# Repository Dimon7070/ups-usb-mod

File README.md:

### Modification in progress
Plans:
- [x] Added Gerber and BOM for original schematic
- [x] Added schematic, Gerber and BOM for 0402 smd parts and ADUM1201 isolator
- [ ] add scematics with SMD sizes that are more hand-soldering friendly.
- [ ] add gerber files 
- [ ] add wiki with explanation about USB-Serial IC setup

# original README
# ups-usb
This repo contains the isolated USB to serial board that I designed for a Serioux LD600LI UPS to get it to talk reliably with NUT.
Project was designed using Kicad V8.  For more information check out [Voltlog #503](https://youtu.be/ZeoCBQmW2Rw)

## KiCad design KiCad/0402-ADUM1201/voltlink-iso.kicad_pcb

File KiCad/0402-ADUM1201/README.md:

Schematics with 0402 smd components and ADUM1201 isolator

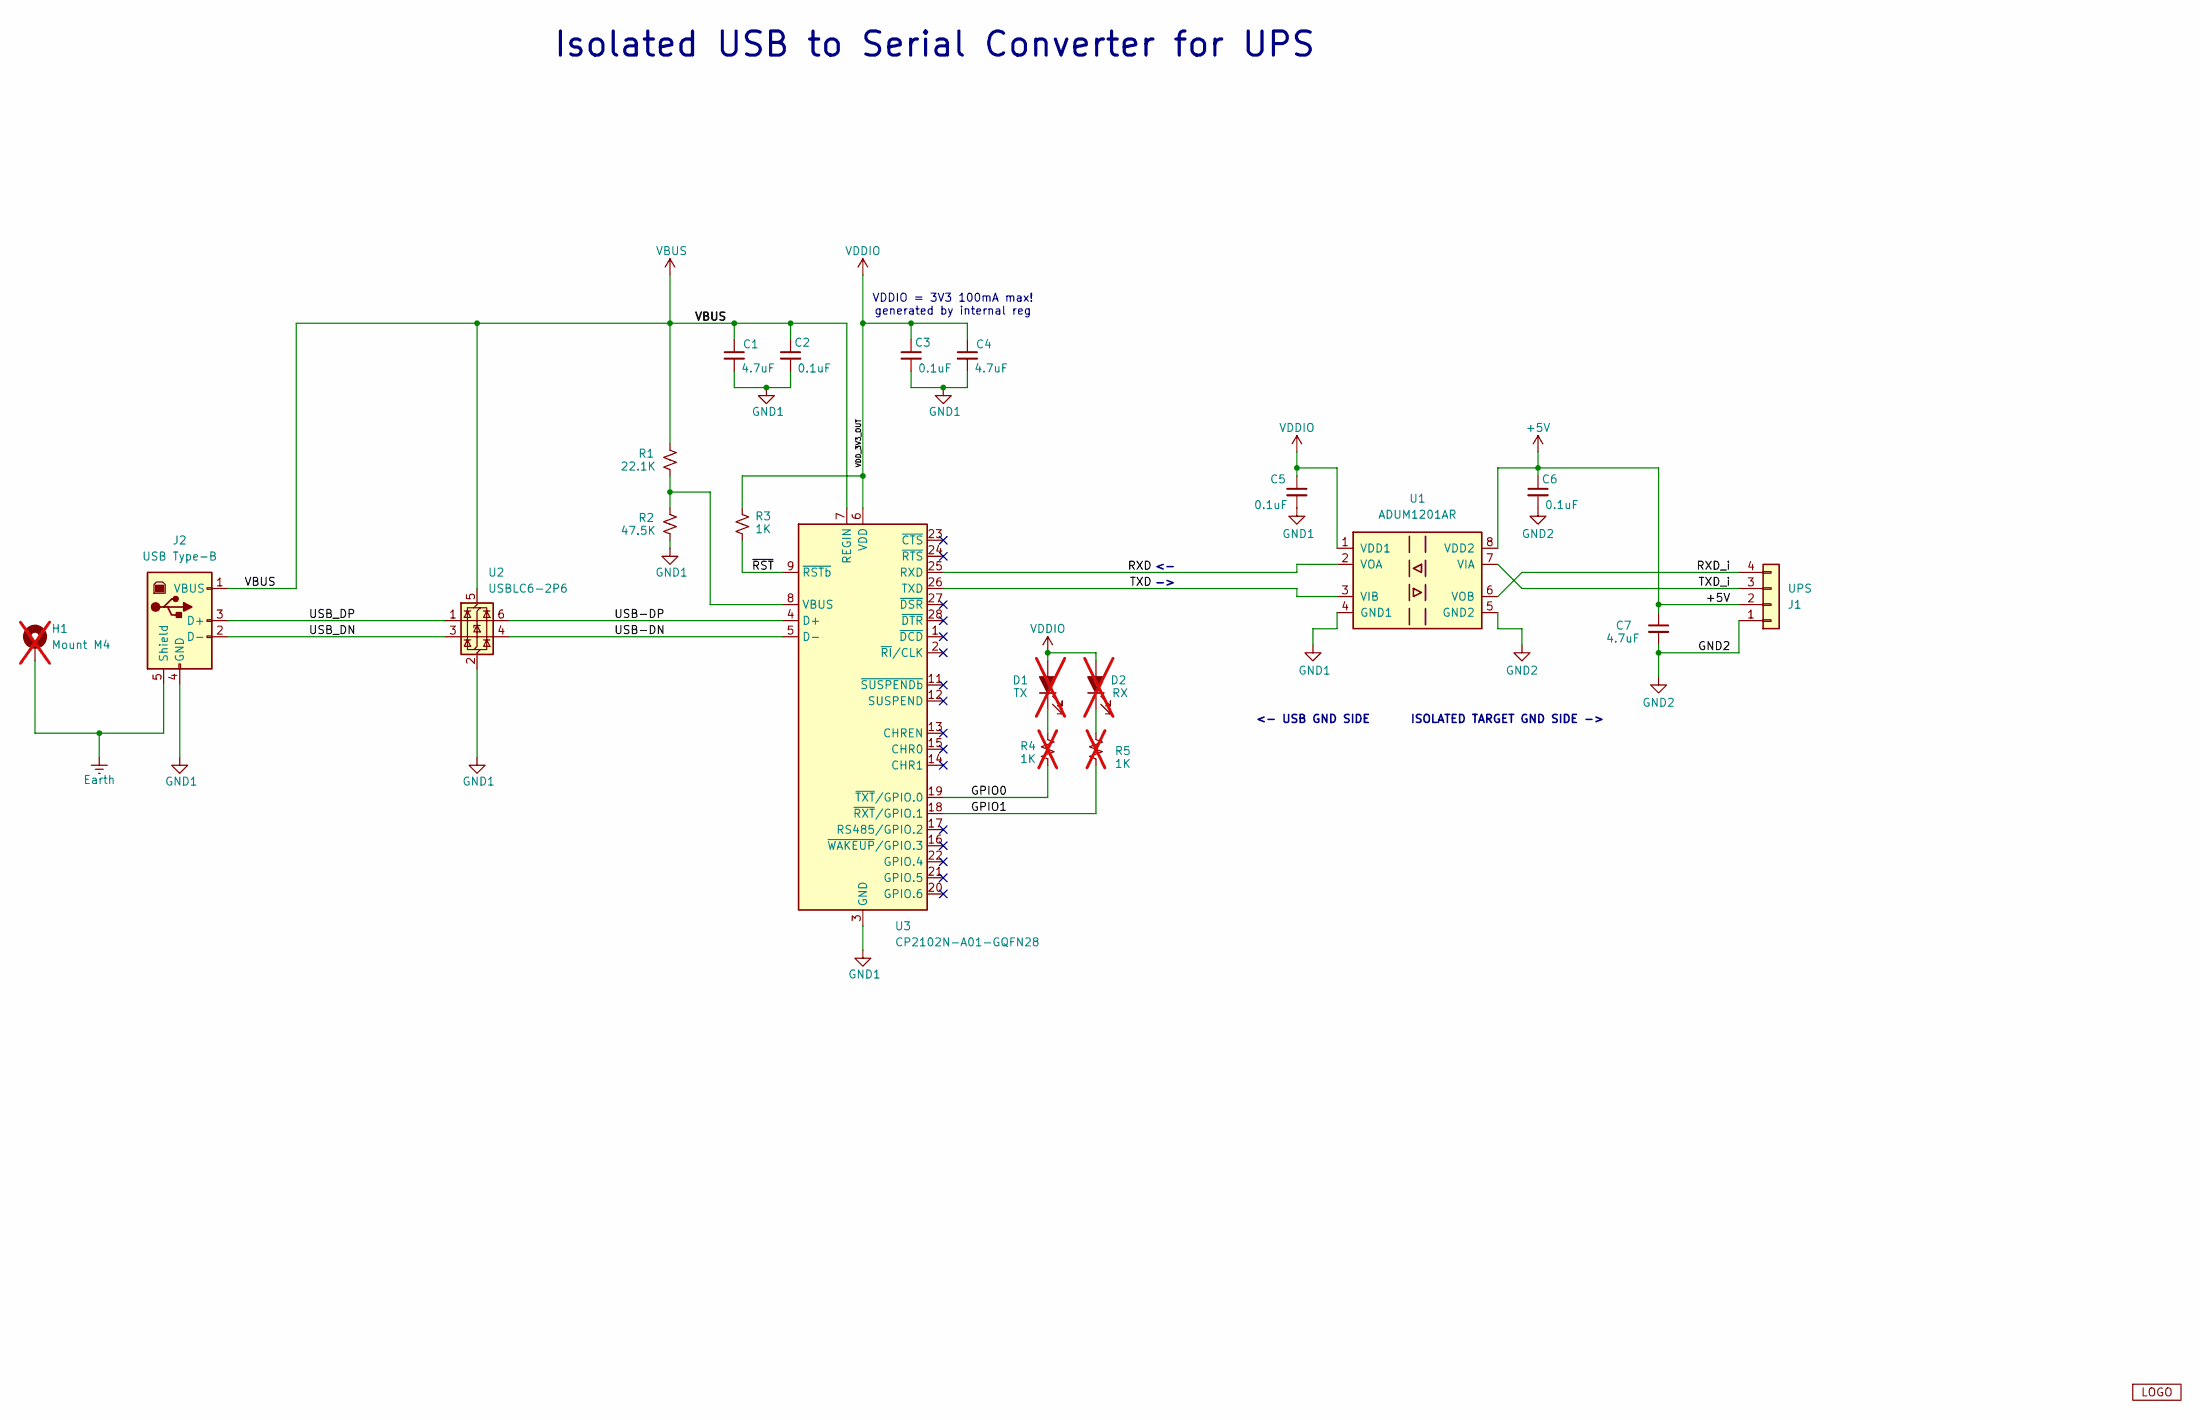
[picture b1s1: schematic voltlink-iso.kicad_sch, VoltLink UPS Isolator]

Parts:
C1, C4, C7: 4.7uF; C_0402_1005Metric; Voltage 10V; LCSC C23733
C2, C3, C5, C6: 0.1uF; C_0402_1005Metric; Voltage 50V; LCSC C307331
D1: TX; LED_0402_1005Metric; LCSC C130723; not fitted
D2: RX; LED_0402_1005Metric; LCSC C130719; not fitted
H1: Mount M4; M4_TH_terminal; not fitted
J1: UPS; JST_XH_B4B-XH-A_1x04_P2.50mm_Vertical; LCSC C19271370
J2: USB Type-B; USB_B_Lumberg_2411_02_Horizontal; LCSC C720549
R1: 22.1K; R_0402_1005Metric; LCSC C43473
R2: 47.5K; R_0402_1005Metric; LCSC C25896
R3: 1K; R_0402_1005Metric; LCSC C11702
R4, R5: 1K; R_0402_1005Metric; LCSC C11702; not fitted
U1: ADUM1201AR; SOIC-8_3.9x4.9mm_P1.27mm; LCSC C9669
U2: USBLC6-2P6; SOT-666; LCSC C2827693
U3: CP2102N-A01-GQFN28; QFN-28-1EP_5x5mm_P0.5mm_EP3.35x3.35mm; LCSC C1550553
V1: VOLTLOG_LOGO; voltlog_silk_5mm

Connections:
+5V: C6.1, C7.1, J1.2, U1.8 (VDD2)
/GPIO0: R4.1, U3.19 (~TXT/GPIO.0)
/GPIO1: R5.1, U3.18 (~RXT/GPIO.1)
/RXD: U1.2 (VOA), U3.25 (RXD)
/RXD_i: J1.4, U1.6 (VOB)
/TXD: U1.3 (VIB), U3.26 (TXD)
/TXD_i: J1.3, U1.7 (VIA)
/USB-DN: U2.4 (I/O2), U3.5 (D-)
/USB-DP: U2.6 (I/O1), U3.4 (D+)
/USB_DN: J2.2 (D-), U2.3 (I/O2)
/USB_DP: J2.3 (D+), U2.1 (I/O1)
/~RST: R3.1, U3.9 (~RSTb)
Earth: H1.1, J2.5 (Shield)
GND1: C1.2, C2.2, C3.2, C4.2, C5.2, J2.4 (GND), R2.2, U1.4 (GND1), U2.2 (GND), U3.3 (GND), U3.29 (GND)
GND2: C6.2, C7.2, J1.1, U1.5 (GND2)
unnamed: D1.1 (K), R4.2
unnamed: D2.1 (K), R5.2
unnamed: R1.2, R2.1, U3.8 (VBUS)
VBUS: C1.1, C2.1, J2.1 (VBUS), R1.1, U2.5 (VBUS), U3.7 (REGIN)
VDDIO: C3.1, C4.1, C5.1, D1.2 (A), D2.2 (A), R3.2, U1.1 (VDD1), U3.6 (VDD)

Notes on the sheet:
Isolated USB to Serial Converter for UPS
<- USB GND SIDE
ISOLATED TARGET GND SIDE ->
VDDIO = 3V3 100mA max! generated by internal reg

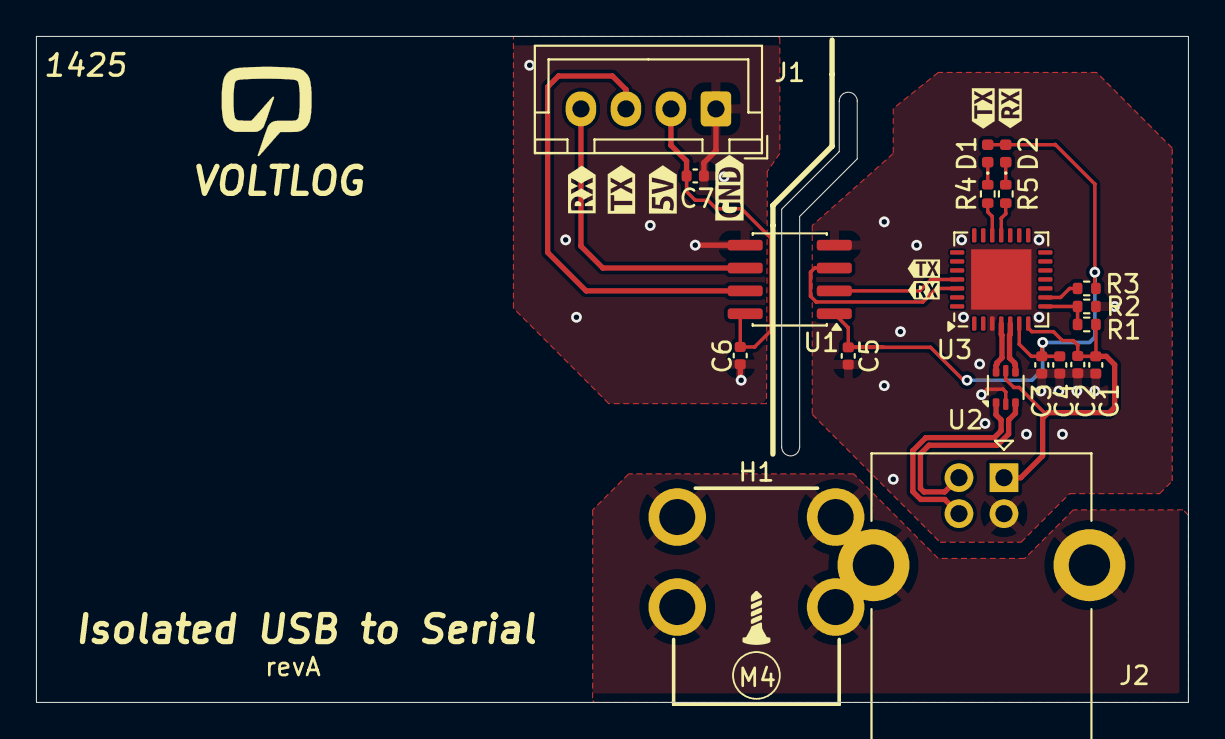
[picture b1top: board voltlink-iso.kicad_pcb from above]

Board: 2 copper layers, 64.0 x 37.0 mm, 29 parts (0 on the bottom side), 20 nets.

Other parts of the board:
kibuzzard-67EF7DAE: G***; kibuzzard-67EF7DAE
kibuzzard-67EF7DB2: G***; kibuzzard-67EF7DB2
kibuzzard-67EF87AE: G***; kibuzzard-67EF87AE
kibuzzard-67EF88A2: G***; kibuzzard-67EF88A2
kibuzzard-67EF879C: G***; kibuzzard-67EF879C
kibuzzard-67EF8788: G***; kibuzzard-67EF8788
kibuzzard-67EF8792: G***; kibuzzard-67EF8792
kibuzzard-67EF8898: G***; kibuzzard-67EF8898

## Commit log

2025-12-13 Folder structure and simple description for KiCad projects
2025-12-13 Moved original schematicd to corresponding folder
2025-12-13 Remove files from old location
2025-12-13 Readme update
2025-12-13 Gerber folder
2025-12-13 added gerbers
2025-12-31 Update README.md
    Added plans for this repo
2026-01-20 added BOM file
2026-01-21 Added ADUM1201 schematic variant
2026-01-21 Modified ADUM1201 schematic, added BOM and Gerbers
2026-01-21 Update README with completed tasks and new plans
    Updated README to reflect completed tasks and plans.

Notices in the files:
KiCad/0402-ADUM1201/voltlink-iso.kicad_sch:
Copyright Voltlog 2025
License: GPLv3
